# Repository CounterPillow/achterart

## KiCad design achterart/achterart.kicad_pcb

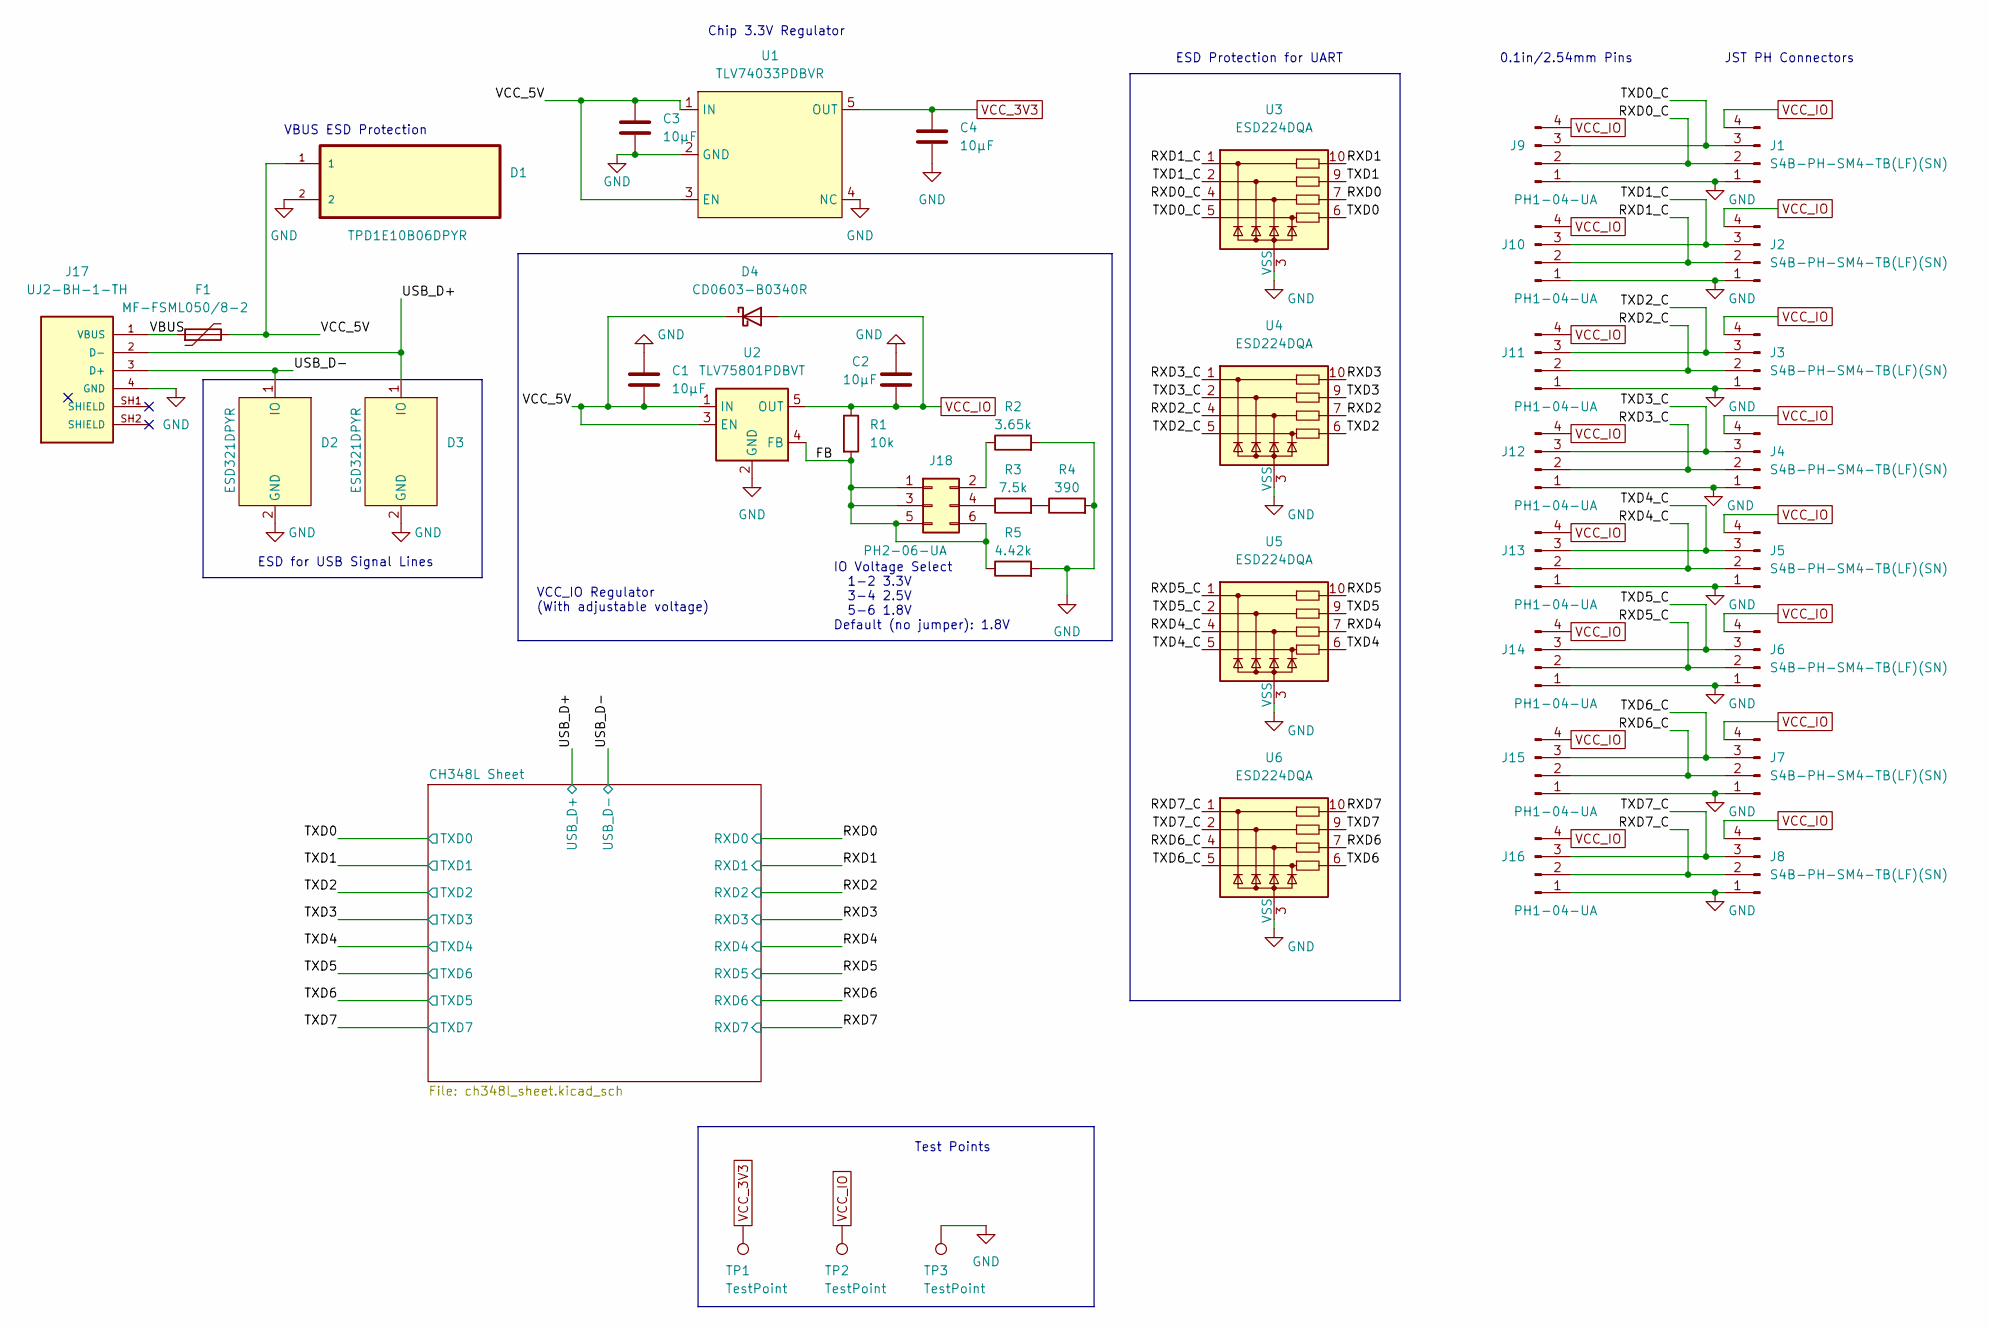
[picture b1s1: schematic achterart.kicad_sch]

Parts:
C1, C2, C3, C4: 10µF; C_0603_1608Metric; MPN 10uF X7R 0603
D1: TPD1E10B06DPYR; DIO_TPD1E05U06DPYR; MPN TPD1E10B06DPYR
D2, D3: ESD321DPYR; DIO_TPD1E05U06DPYR; MPN ESD321DPYR
D4: CD0603-B0340R; D_0603_1608Metric; MPN CD0603-B0340R
F1: MF-FSML050/8-2; Fuse_0603_1608Metric; MPN MF-FSML050/8-2
J1, J2, J3, J4, J5, J6, J7, J8: S4B-PH-SM4-TB(LF)(SN); JST_PH_S4B-PH-SM4-TB_1x04-1MP_P2.00mm_Horizontal; MPN S4B-PH-SM4-TB(LF)(SN)
J9, J10, J11, J12, J13, J14, J15, J16: PH1-04-UA; PinHeader_1x04_P2.54mm_Vertical; MPN PH1-04-UA; LCSC Part # C706876
J17: UJ2-BH-1-TH; CUI_UJ2-BH-1-TH; PART_REV 1.0
J18: PH2-06-UA; PinHeader_2x03_P2.54mm_Vertical; MPN PH2-06-UA; LCSC Part # C706893
R1: 10k; R_0603_1608Metric; MPN 10k 1% 0603
R2: 3.65k; R_0603_1608Metric; MPN 3.65k 1% 0603
R3: 7.5k; R_0603_1608Metric; MPN 7.5k 1% 0603
R4: 390; R_0603_1608Metric; MPN 390 1% 0603
R5: 4.42k; R_0603_1608Metric; MPN 4.42k 1% 0603
TP1, TP2, TP3: TestPoint; TestPoint_Plated_Hole_D2.0mm
U1: TLV74033PDBVR; SOT95P280X145-5N; MPN TLV74033PDBVR
U2: TLV75801PDBVT; SOT-23-5; MPN TLV75801PDBVT
U3, U4, U5, U6: ESD224DQA; Diodes_UDFN-10_1.0x2.5mm_P0.5mm; MPN ESD224DQAR

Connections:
/FB: J18.1, J18.3, J18.5, J18.6, R1.2, R5.1, U2.4 (FB)
/RXD0: U3.7; also elsewhere on the board
/RXD0_C: J1.2, J9.2, U3.4
/RXD1: U3.10; also elsewhere on the board
/RXD1_C: J2.2, J10.2, U3.1
/RXD2: U4.7; also elsewhere on the board
/RXD2_C: J3.2, J11.2, U4.4
/RXD3: U4.10; also elsewhere on the board
/RXD3_C: J4.2, J12.2, U4.1
/RXD4: U5.7; also elsewhere on the board
/RXD4_C: J5.2, J13.2, U5.4
/RXD5: U5.10; also elsewhere on the board
/RXD5_C: J6.2, J14.2, U5.1
/RXD6: U6.7; also elsewhere on the board
/RXD6_C: J7.2, J15.2, U6.4
/RXD7: U6.10; also elsewhere on the board
/RXD7_C: J8.2, J16.2, U6.1
/TXD0: U3.6; also elsewhere on the board
/TXD0_C: J1.3, J9.3, U3.5
/TXD1: U3.9; also elsewhere on the board
/TXD1_C: J2.3, J10.3, U3.2
/TXD2: U4.6; also elsewhere on the board
/TXD2_C: J3.3, J11.3, U4.5
/TXD3: U4.9; also elsewhere on the board
/TXD3_C: J4.3, J12.3, U4.2
/TXD4: U5.6; also elsewhere on the board
/TXD4_C: J5.3, J13.3, U5.5
/TXD5: U5.9; also elsewhere on the board
/TXD5_C: J6.3, J14.3, U5.2
/TXD6: U6.6; also elsewhere on the board
/TXD6_C: J7.3, J15.3, U6.5
/TXD7: U6.9; also elsewhere on the board
/TXD7_C: J8.3, J16.3, U6.2
/USB_D+: D3.1 (IO), J17.2 (D-); also elsewhere on the board
/USB_D-: D2.1 (IO), J17.3 (D+); also elsewhere on the board
/VBUS: F1.1, J17.1 (VBUS)
/VCC_5V: C1.2, C3.1, D1.1, D4.1 (K), F1.2, U1.1 (IN), U1.3 (EN), U2.1 (IN), U2.3 (EN); also elsewhere on the board
GND: C1.1, C2.1, C3.2, C4.2, D1.2, D2.2 (GND), D3.2 (GND), J1.1, J2.1, J3.1, J4.1, J5.1, J6.1, J7.1, J8.1, J9.1, J10.1, J11.1, J12.1, J13.1, J14.1, J15.1, J16.1, J17.4 (GND), R2.2, R4.2, R5.2, TP3.1, U1.2 (GND), U1.4 (NC), U2.2 (GND), U3.3 (VSS), U3.8 (VSS), U4.3 (VSS), U4.8 (VSS), U5.3 (VSS), U5.8 (VSS), U6.3 (VSS), U6.8 (VSS); also elsewhere on the board
unnamed: J18.2, R2.1
unnamed: J18.4, R3.1
unnamed: R3.2, R4.1
VCC_3V3: C4.1, TP1.1, U1.5 (OUT); also elsewhere on the board
VCC_IO: C2.2, D4.2 (A), J1.4, J2.4, J3.4, J4.4, J5.4, J6.4, J7.4, J8.4, J9.4, J10.4, J11.4, J12.4, J13.4, J14.4, J15.4, J16.4, R1.1, TP2.1, U2.5 (OUT); also elsewhere on the board

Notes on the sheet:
ESD for USB Signal Lines
VBUS ESD Protection
VCC_IO Regulator (With adjustable voltage)
0.1in/2.54mm Pins
JST PH Connectors
IO Voltage Select 1-2 3.3V 3-4 2.5V 5-6 1.8V Default (no jumper): 1.8V
Chip 3.3V Regulator
ESD Protection for UART
Test Points

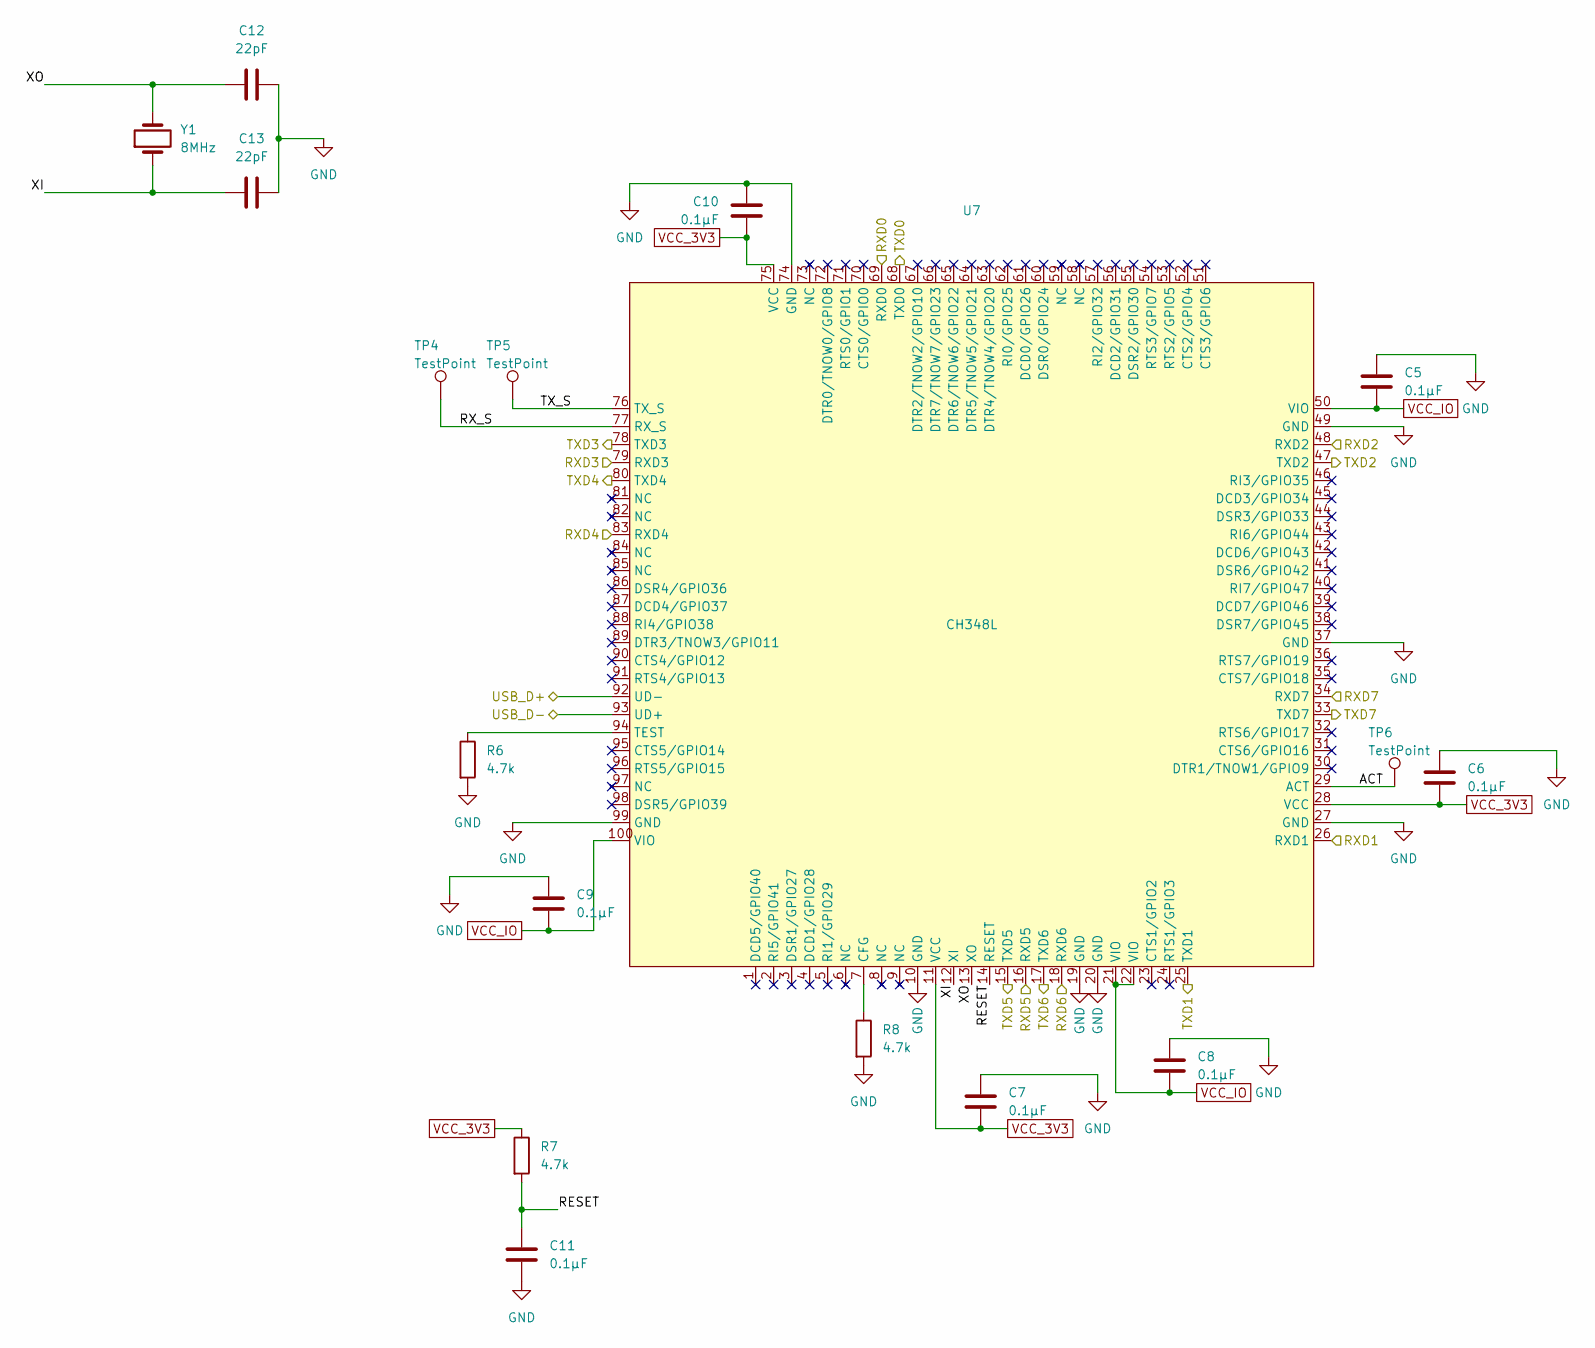
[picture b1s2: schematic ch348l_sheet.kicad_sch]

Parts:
C5, C6, C7, C8, C9, C10, C11: 0.1µF; C_0603_1608Metric; MPN 0.1uF 0603
C12, C13: 22pF; C_0603_1608Metric; MPN 251R14S220JV4T; LCSC Part # C2168905
R6, R7, R8: 4.7k; R_0603_1608Metric; MPN 4.7k 0603
TP4, TP5, TP6: TestPoint; TestPoint_Plated_Hole_D2.0mm
U7: CH348L; LQFP-100_14x14mm_P0.5mm; MPN CH348L; LCSC Part # C2979160
Y1: 8MHz; Crystal_SMD_HC49-SD_HandSoldering; MPN ATS080BSM-1E

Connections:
/CH348L Sheet/ACT: TP6.1, U7.29 (ACT)
/CH348L Sheet/RESET: C11.1, R7.2, U7.14 (RESET)
/CH348L Sheet/RX_S: TP4.1, U7.77 (RX_S)
/CH348L Sheet/TX_S: TP5.1, U7.76 (TX_S)
/CH348L Sheet/XI: C13.1, U7.12 (XI), Y1.1
/CH348L Sheet/XO: C12.1, U7.13 (XO), Y1.2
/RXD0: U7.69 (RXD0); also elsewhere on the board
/RXD1: U7.26 (RXD1); also elsewhere on the board
/RXD2: U7.48 (RXD2); also elsewhere on the board
/RXD3: U7.79 (RXD3); also elsewhere on the board
/RXD4: U7.83 (RXD4); also elsewhere on the board
/RXD5: U7.16 (RXD5); also elsewhere on the board
/RXD6: U7.18 (RXD6); also elsewhere on the board
/RXD7: U7.34 (RXD7); also elsewhere on the board
/TXD0: U7.68 (TXD0); also elsewhere on the board
/TXD1: U7.25 (TXD1); also elsewhere on the board
/TXD2: U7.47 (TXD2); also elsewhere on the board
/TXD3: U7.78 (TXD3); also elsewhere on the board
/TXD4: U7.80 (TXD4); also elsewhere on the board
/TXD5: U7.17 (TXD6); also elsewhere on the board
/TXD6: U7.15 (TXD5); also elsewhere on the board
/TXD7: U7.33 (TXD7); also elsewhere on the board
/USB_D+: U7.92 (UD-); also elsewhere on the board
/USB_D-: U7.93 (UD+); also elsewhere on the board
GND: C5.1, C6.1, C7.1, C8.1, C9.1, C10.1, C11.2, C12.2, C13.2, R6.2, R8.2, U7.10 (GND), U7.19 (GND), U7.20 (GND), U7.27 (GND), U7.37 (GND), U7.49 (GND), U7.74 (GND), U7.99 (GND); also elsewhere on the board
unnamed: R6.1, U7.94 (TEST)
unnamed: R8.1, U7.7 (CFG)
VCC_3V3: C6.2, C7.2, C10.2, R7.1, U7.11 (VCC), U7.28 (VCC), U7.75 (VCC); also elsewhere on the board
VCC_IO: C5.2, C8.2, C9.2, U7.21 (VIO), U7.22 (VIO), U7.50 (VIO), U7.100 (VIO); also elsewhere on the board

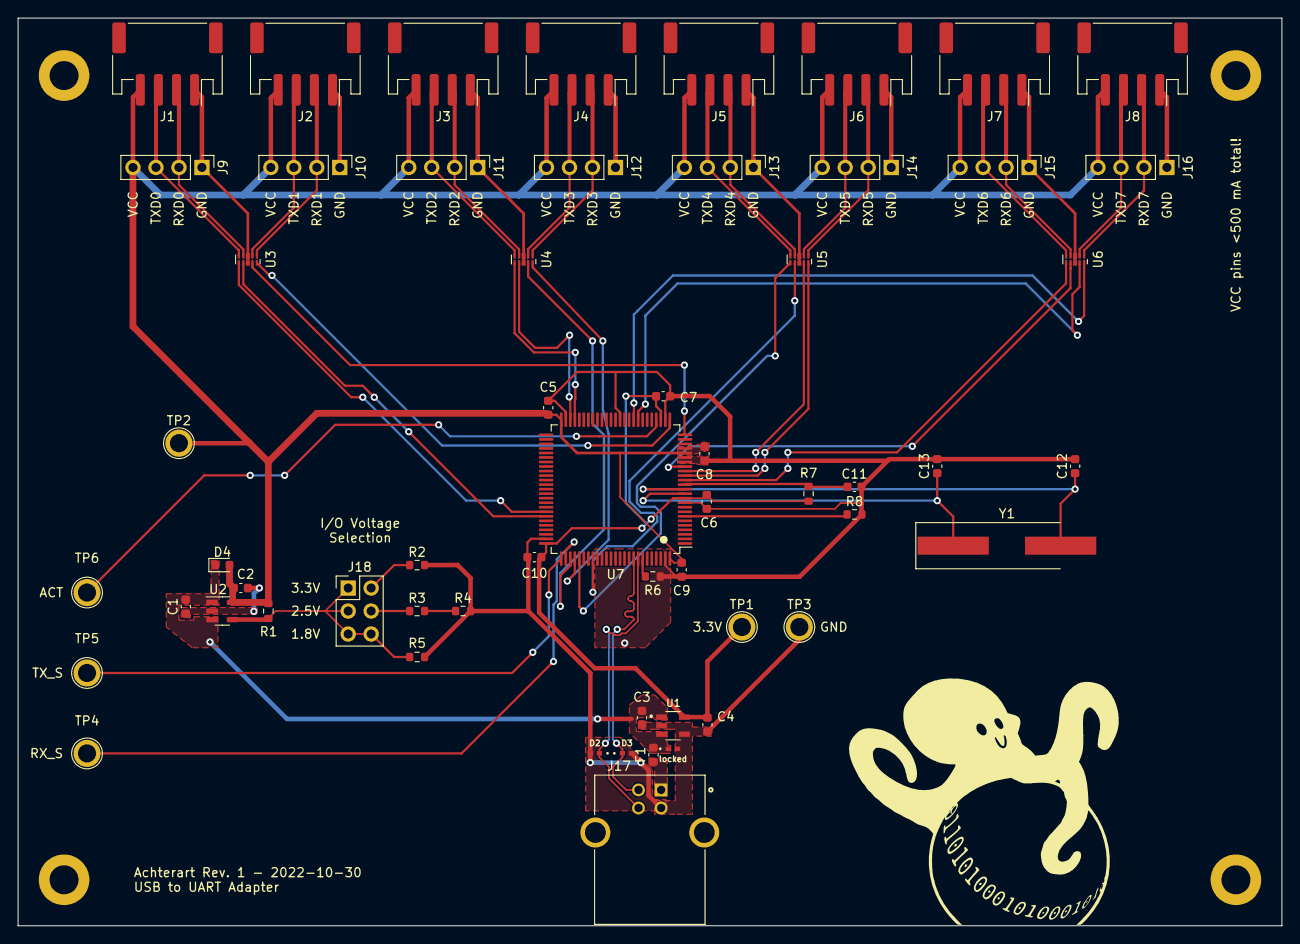
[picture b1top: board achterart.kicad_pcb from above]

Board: 2 copper layers, 139.7 x 100.3 mm, 58 parts (0 on the bottom side), 51 nets.

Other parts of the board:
locked: TPD1E10B06DPYR; DIO_TPD1E05U06DPYR

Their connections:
/VCC_5V: locked.1; also elsewhere on the board
GND: locked.2; also elsewhere on the board

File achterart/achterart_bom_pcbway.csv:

Item #,Designator,Qty,Manufacturer,Mfg Part #,Description / Value,Package,Type,Comments
1,D1,1,Texas Instruments,TPD1E10B06DPYR,IC ESD Protection 2-X1SON ,2-X1SON,SMD,
2,"C12,C13",2,Johanson Technology Inc.,251R14S220JV4T,Cap 22pF High Frequency 0603,0603,SMD,
3,"J12,J13,J10,J16,J11,J14,J15,J9",8,Adam Tech,PH1-04-UA,Conn Header 4Pos 2.54mm Vert Gold,PinHeader_1x04_P2.54mm_Vertical,Thru-hole,
4,"J3,J1,J8,J6,J5,J7,J2,J4",8,JST Sales America Inc.,S4B-PH-SM4-TB(LF)(SN),Conn JST PH 4Pos Horizontal,JST_PH_S4B-PH-SM4-TB_1x04-1MP_P2.00mm_Horizontal,SMD,
5,"C9,C10,C6,C11,C7,C5,C8",7,,0.1uF 0603,Cap 0.1uF 0603,0603,SMD,
6,"C4,C3,C2,C1",4,,10uF X7R 0603,Cap 10uF X7R 0603,0603,SMD,
7,"D2,D3",2,Texas Instruments,ESD321DPYR,IC ESD Protection 2-X1SON ,2-X1SON,SMD,
8,D4,1,Bourns Inc.,CD0603-B0340R,Diode Schottky 0603,0603,SMD,
9,"R6,R8,R7",3,,4.7k 0603,Res 4.7k Ohm 0603,0603,SMD,
10,"U3,U5,U6,U4",4,Texas Instruments,ESD224DQAR,TVS DIODE 3.6VWM 14VC USON-10,USON-10,SMD,
11,R2,1,,3.65k 1% 0603,Res 3.65k 1% 0603,0603,SMD,
12,R5,1,,4.42k 1% 0603,Res 4.42k 1% 0603,0603,SMD,
13,J17,1,CUI Inc.,UJ2-BH-1-TH,Conn USB Type-B Thru-Hole,CUI_UJ2-BH-1-TH,Thru-hole,
14,F1,1,Bourns Inc.,MF-FSML050/8-2,Fuse 500 mA Hold 1A Trip 0603,0603,SMD,
15,R1,1,,10k 1% 0603,Res 10k 1% 0603,0603,SMD,
16,R4,1,,390 1% 0603,Res 390 1% 0603,0603,SMD,
17,U2,1,Texas Instruments,TLV75801PDBVT,IC Voltage Regulator SOT-23-5,SOT-23-5,SMD,
18,Y1,1,CTS-Frequency Controls,ATS080BSM-1E,Crystal 8 MHz SMD HC49,SMD_HC49-SD,SMD,
19,U7,1,WCH,CH348L,IC 8-channel USB-to-UART LQFP-100,LQFP-100_14x14mm_P0.5mm,SMD,
20,U1,1,Texas Instruments,TLV74033PDBVR,IC Voltage Regulator SOT-23-5,SOT-23-5,SMD,
21,R3,1,,7.5k 1% 0603,Res 7.5k 1% 0603,0603,SMD,
22,J18,1,Adam Tech,PH2-06-UA,Conn Header 2x3Pos 2.54mm Vert Gold,PinHeader_2x03_P2.54mm_Vertical,Thru-hole,

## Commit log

2022-10-31 Add JST 3d model
    Pretty sure I can't distribute it, so it's just gonna be useless
    to everyone not on my computer.
2022-11-14 Add some more measurements on the user drawings layer
